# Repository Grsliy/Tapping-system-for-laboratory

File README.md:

# Sistem Logbook Pengunjung Lab berbasis RFID

Sistem pencatatan kunjungan otomatis untuk Laboratorium Power Electronics. Pengunjung yang
sudah terdaftar tinggal tap kartu RFID di pintu masuk, tanpa perlu isi buku tamu fisik.

## Cara kerja

1. Pengunjung mengajukan surat izin kunjungan ke lab, lalu admin mendaftarkan namanya ke
   Google Sheet bersama UID kartu RFID yang akan dipakai.
2. Saat berkunjung, pengunjung tap kartu di reader RFID yang terpasang di pintu masuk.
3. ESP32 membaca UID kartu dan mengirimkannya ke Google Apps Script lewat HTTPS.
4. Apps Script mencocokkan UID ke daftar pengunjung terdaftar, lalu mencatat waktu tap ke
   Google Sheet.
5. Layar pada perangkat menyapa pengunjung dengan namanya, atau memberi tahu bahwa kartunya
   belum terdaftar.

Rincian tiap langkah ada di bagian [Cara Kerja](Dokumen/Sistem-Logbook-Pengunjung-RFID.md#cara-kerja)
di dokumen utama.

## Arsitektur

ESP32 membaca UID kartu lewat modul MFRC522, connect ke jaringan WiFi kampus, lalu
mengirim data tap ke Google Apps Script yang mencocokkan dan mencatatnya ke Google Sheet.
Hasilnya ditampilkan di layar OLED pada perangkat, sehingga alat ini berdiri sendiri di
pintu masuk tanpa komputer yang tersambung.

Detail lengkap arsitektur, varian ESP32 yang dipakai, keputusan teknis, dan skema data ada
di [Dokumen/Sistem-Logbook-Pengunjung-RFID](Dokumen/Sistem-Logbook-Pengunjung-RFID.md).

## Struktur folder

- [Dokumen/](Dokumen/) — rancangan sistem, keputusan arsitektur, dan milestone pengerjaan.
- [Tutorial/](Tutorial/) — panduan langkah kerja per milestone, urut sesuai hari pengerjaan.
- [Referensi/](Referensi/) — materi pendukung (modul praktikum IoT, datasheet modul MFRC522).
- [Gambar/](Gambar/) — foto prototipe, diagram arsitektur, dan skematik rangkaian.
- [PCB/](PCB/) — PCB satu sisi 46×48 mm: berkas KiCad, Gerber, PDF untuk toner transfer, dan
  script pembangunnya.
- [Casing/](Casing/) — casing cetak 3D berbentuk kucing yang memikul kotak elektronik, beserta
  ilustrasi letak PCB di dalamnya. Model kucingnya remix dari
  [Cute Cat Phone Holder](https://www.thingiverse.com/thing:7095121) karya ABoyNamedSue
  (CC BY-SA).
- [logbook-firmware/](logbook-firmware/) — kode firmware ESP32 (PlatformIO, framework Arduino).
- [logbook-appsscript/](logbook-appsscript/) — salinan lokal kode Google Apps Script (backend
  yang jalan di Google, dipakai untuk riwayat/backup di luar Apps Script Editor).

## Status pengerjaan

Status terkini ada di bagian [Status dan Rencana Kerja](Dokumen/Sistem-Logbook-Pengunjung-RFID.md#status-dan-rencana-kerja)
di dokumen utama.

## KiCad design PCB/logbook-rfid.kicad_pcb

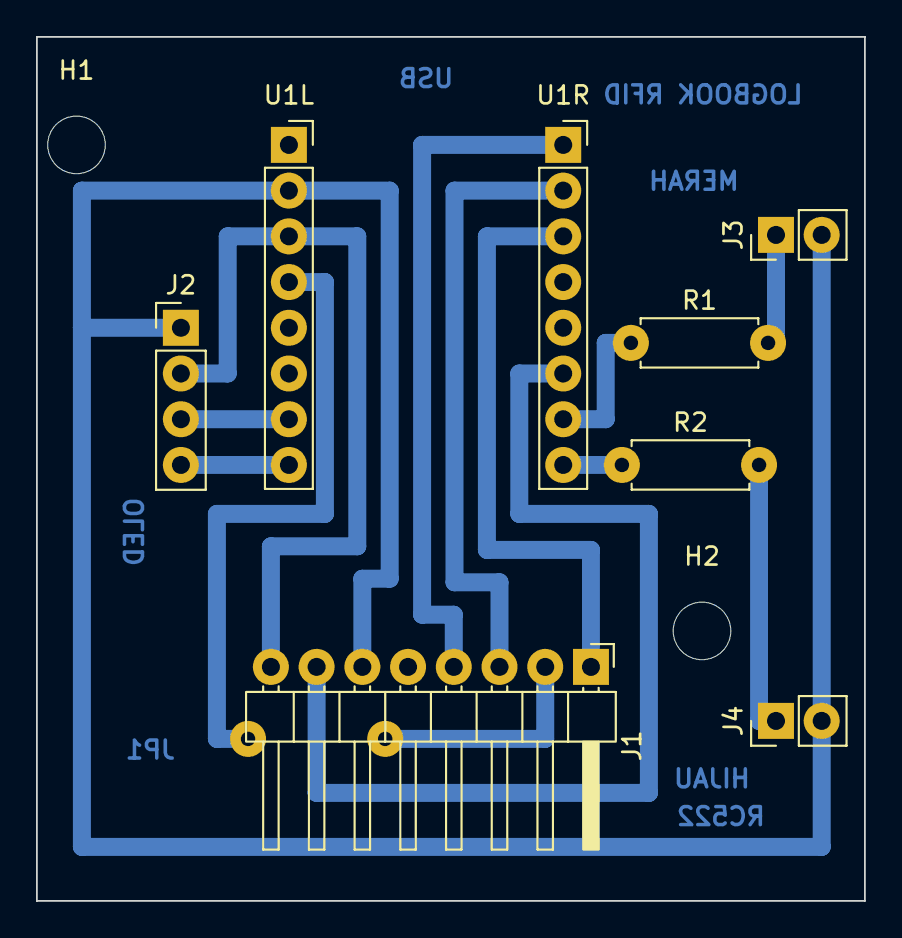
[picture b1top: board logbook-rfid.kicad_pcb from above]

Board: 2 copper layers, 46.0 x 48.0 mm, 11 parts (1 on the bottom side), 13 nets.

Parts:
H1, H2: M3; MountingHole_3.2mm_M3
J1: RC522; PinHeader_1x08_P2.54mm_Horizontal
J2: OLED (solder); PinHeader_1x04_P2.54mm_Vertical
J3: LED merah (solder); PinHeader_1x02_P2.54mm_Vertical
J4: LED hijau (solder); PinHeader_1x02_P2.54mm_Vertical
JP1: kabel berisolasi; R_Axial_DIN0207_L6.3mm_D2.5mm_P7.62mm_Horizontal
R1, R2: 220; R_Axial_DIN0207_L6.3mm_D2.5mm_P7.62mm_Horizontal
U1L: SuperMini kiri; PinSocket_1x08_P2.54mm_Vertical
U1R: SuperMini kanan; PinSocket_1x08_P2.54mm_Vertical

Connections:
3V3: J1.8, J2.2, U1L.3
CS: J1.1, U1R.3
GND: J1.6, J2.1, J3.2, J4.2, U1L.2
LED_G: R2.1, U1R.8
LED_G_A: J4.1, R2.2
LED_R: R1.1, U1R.7
LED_R_A: J3.1, R1.2
MISO: J1.4, U1R.1
MOSI: J1.3, U1R.2
RST: J1.7, U1R.6
SCK: J1.2, JP1.1, U1L.4
SCL: J2.3, U1L.7
SDA: J2.4, U1L.8

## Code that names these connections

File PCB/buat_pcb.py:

"""Bangun PCB single-layer (B.Cu) logbook RFID versi compact, dengan routing manual.

Disesuaikan dengan casing Casing/kucing-kotak-menyatu yang sudah dicetak: PCB di lantai bak, di
bawah modul OLED, komponen menghadap atas, tepi USB menghadap dinding kanan bak. Posisi di bak:
u = 23 - y_pcb, v = 92.2 - x_pcb. Ruang di atas PCB 15.9 mm (di bawah OLED) sampai 20.4 mm. Karena itu:
  lubang M3 di (2.2, 6) dan (36.95, 33), tepat di atas standoff bak (17, 90) dan (-10, 55.25)
  J1 (RC522) header siku, pin rebah ke tepi bawah PCB, dupont menjulur ke dinding kiri bak
  J2 (OLED), J3 (LED merah), dan J4 (LED hijau) tanpa header, kabel disolder langsung ke pad
  (J2 di bawah modul OLED dan dekat dinding belakang bak, tidak ada ruang untuk dupont)
  J3 di sisi kanan bak dan J4 di sisi kiri, searah dengan letak LED merah dan hijau di tutup
  JP1 kabel jumper berisolasi di sisi bawah PCB (sisi atas tertutup dupont J1)
Resistor LED THT tidur di PCB, LED di tutup casing.
"""
import sys
import pcbnew
from pcbnew import VECTOR2I_MM as P, FromMM

out = sys.argv[1]
# Mode 'milling': routing sama, tapi ground fill disederhanakan untuk software CNC yang hang pada
# poligon rumit: tanpa teks tembaga, pad GND tersambung penuh (tanpa thermal relief), dan
# lingkaran dipecah lebih kasar.
MILLING = len(sys.argv) > 2 and sys.argv[2] == 'milling'
LIB = r'C:/Program Files/KiCad/10.0/share/kicad/footprints/'
TRACK_W = 1.0
PAD_D = 2.0
BOARD_W, BOARD_H = 46, 48

b = pcbnew.BOARD()
ds = b.GetDesignSettings()
ds.m_MinClearance = FromMM(0.4)
ds.m_TrackMinWidth = FromMM(0.8)
if MILLING:
    ds.m_MaxError = FromMM(0.05)
ds.SetCopperLayerCount(2)

nets = {}
def net(name):
    if name not in nets:
        n = pcbnew.NETINFO_ITEM(b, name)
        b.Add(n)
        nets[name] = n
    return nets[name]

def place(lib, name, ref, value, x, y, rot=0, pad_d=PAD_D):
    fp = pcbnew.FootprintLoad(LIB + lib + '.pretty', name)
    fp.SetReference(ref)
    fp.SetValue(value)
    b.Add(fp)
    fp.SetPosition(P(x, y))
    fp.SetOrientationDegrees(rot)
    if pad_d:
        for p in fp.Pads():
            p.SetSize(pcbnew.F_Cu, P(pad_d, pad_d))
    return fp

def pos(p):
    q = p.GetPosition()
    return (round(pcbnew.ToMM(q.x), 3), round(pcbnew.ToMM(q.y), 3))

def pin(fp, num, netname):
    p = fp.FindPadByNumber(str(num))
    p.SetNet(net(netname))
    return pos(p)

def track(netname, *pts):
    for a, c in zip(pts, pts[1:]):
        t = pcbnew.PCB_TRACK(b)
        t.SetStart(P(*a))
        t.SetEnd(P(*c))
        t.SetWidth(FromMM(TRACK_W))
        t.SetLayer(pcbnew.B_Cu)
        t.SetNet(net(netname))
        b.Add(t)

def text(s, x, y, size=1.0, rot=0):
    t = pcbnew.PCB_TEXT(b)
    t.SetText(s)
    t.SetPosition(P(x, y))
    t.SetLayer(pcbnew.B_Cu)
    t.SetMirrored(True)
    t.SetTextSize(P(size, size))
    t.SetTextThickness(FromMM(0.2))
    t.SetTextAngleDegrees(rot)
    b.Add(t)

# ===== Komponen =====
# ESP32-C3 SuperMini dilihat dari atas, USB menghadap ke atas (y kecil)
uL = place('Connector_PinSocket_2.54mm', 'PinSocket_1x08_P2.54mm_Vertical', 'U1L', 'SuperMini kiri', 14, 6)
uR = place('Connector_PinSocket_2.54mm', 'PinSocket_1x08_P2.54mm_Vertical', 'U1R', 'SuperMini kanan', 29.24, 6)
# J1 pin 1 = SDA RC522 di ujung kanan, pin 8 = 3.3V di ujung kiri; header siku, pin rebah ke +y
# (tepi bawah papan) karena tepat di atasnya ada modul OLED
j1 = place('Connector_PinHeader_2.54mm', 'PinHeader_1x08_P2.54mm_Horizontal', 'J1', 'RC522', 30.78, 35, 270)
# J2 ke OLED, tanpa header (kabel disolder langsung). Urutan mengikuti modul OLED yang dipakai:
# GND, VDD, SCK, SDA (modul lain ada yang VCC, GND, ...; cek label modul sebelum menyambung)
j2 = place('Connector_PinHeader_2.54mm', 'PinHeader_1x04_P2.54mm_Vertical', 'J2', 'OLED (solder)', 8, 16.16)
# Pad solder LED (anoda, GND), dipisah supaya masing-masing dekat LED-nya di tutup casing:
# J3 merah di dekat tepi atas PCB (sisi kanan bak), J4 hijau di dekat tepi bawah (sisi kiri bak).
j3 = place('Connector_PinHeader_2.54mm', 'PinHeader_1x02_P2.54mm_Vertical', 'J3', 'LED merah (solder)', 41.06, 11, 90)
j4 = place('Connector_PinHeader_2.54mm', 'PinHeader_1x02_P2.54mm_Vertical', 'J4', 'LED hijau (solder)', 41.06, 38, 90)
r1 = place('Resistor_THT', 'R_Axial_DIN0207_L6.3mm_D2.5mm_P7.62mm_Horizontal', 'R1', '220', 33, 17)
r2 = place('Resistor_THT', 'R_Axial_DIN0207_L6.3mm_D2.5mm_P7.62mm_Horizontal', 'R2', '220', 32.5, 23.78)
jp1 = place('Resistor_THT', 'R_Axial_DIN0207_L6.3mm_D2.5mm_P7.62mm_Horizontal', 'JP1', 'kabel berisolasi', 11.73, 39)
# Sisi atas di titik ini tertutup dupont J1, jadi JP1 dipasang di sisi bawah (ruang standoff 5 mm)
# sebagai kabel berisolasi. Dibalik atas-bawah supaya posisi pad tetap.
jp1.Flip(jp1.GetPosition(), pcbnew.FLIP_DIRECTION_TOP_BOTTOM)
# Dua pad bernomor sama = disambung kabel, supaya DRC tidak menganggapnya putus
jp1.SetDuplicatePadNumbersAreJumpers(True)
jp1.FindPadByNumber('2').SetNumber('1')
HOLES = [(2.2, 6), (36.95, 33)]   # di atas standoff bak yang sudah dicetak
for i, (x, y) in enumerate(HOLES):
    place('MountingHole', 'MountingHole_3.2mm_M3', f'H{i+1}', 'M3', x, y, pad_d=None)

# ===== Pad ke net =====
L = {2: pin(uL, 2, 'GND'), 3: pin(uL, 3, '3V3'), 4: pin(uL, 4, 'SCK'),
     7: pin(uL, 7, 'SCL'), 8: pin(uL, 8, 'SDA')}
R = {1: pin(uR, 1, 'MISO'), 2: pin(uR, 2, 'MOSI'), 3: pin(uR, 3, 'CS'),
     6: pin(uR, 6, 'RST'), 7: pin(uR, 7, 'LED_R'), 8: pin(uR, 8, 'LED_G')}
J1 = {1: pin(j1, 1, 'CS'), 2: pin(j1, 2, 'SCK'), 3: pin(j1, 3, 'MOSI'), 4: pin(j1, 4, 'MISO'),
      6: pin(j1, 6, 'GND'), 7: pin(j1, 7, 'RST'), 8: pin(j1, 8, '3V3')}
J2 = {1: pin(j2, 1, 'GND'), 2: pin(j2, 2, '3V3'), 3: pin(j2, 3, 'SCL'), 4: pin(j2, 4, 'SDA')}
J3 = {1: pin(j3, 1, 'LED_R_A'), 2: pin(j3, 2, 'GND')}
J4 = {1: pin(j4, 1, 'LED_G_A'), 2: pin(j4, 2, 'GND')}
R1 = (pin(r1, 1, 'LED_R'), pin(r1, 2, 'LED_R_A'))
R2 = (pin(r2, 1, 'LED_G'), pin(r2, 2, 'LED_G_A'))
for p in jp1.Pads():
    p.SetNet(net('SCK'))
JP = tuple(sorted(pos(p) for p in jp1.Pads()))
print('J1', J1); print('J3', J3); print('R1', R1, 'R2', R2); print('JP', JP)

# ===== Routing B.Cu =====
# I2C langsung ke kiri
track('SCL', L[7], J2[3])
track('SDA', L[8], J2[4])
# 3V3: ke OLED (J2 pin 2) masuk dari kanan, ke RC522 lewat bawah modul
track('3V3', L[3], (10.6, 11.08), (10.6, 18.70), J2[2])
track('3V3', L[3], (17.8, 11.08), (17.8, 28.3), (13, 28.3), J1[8])
# GND: ke OLED (J2 pin 1) dan LED lewat tepi papan, ke RC522 lewat bawah modul
track('GND', L[2], (2.5, 8.54), (2.5, 16.16), J2[1])
track('GND', (2.5, 16.16), (2.5, 45), (43.6, 45), J4[2])
track('GND', J4[2], J3[2])
track('GND', L[2], (19.6, 8.54), (19.6, 30.1), (18.08, 30.1), J1[6])
# SPI
track('MISO', R[1], (21.4, 6), (21.4, 32.1), (23.16, 32.1), J1[4])
track('MOSI', R[2], (23.2, 8.54), (23.2, 30.3), (25.70, 30.3), J1[3])
track('CS', R[3], (25.0, 11.08), (25.0, 28.5), (30.78, 28.5), J1[1])
track('SCK', L[4], (16.0, 13.62), (16.0, 26.5), (10, 26.5), (10, 39), JP[0])
track('SCK', JP[1], (28.24, 39), J1[2])
track('RST', R[6], (26.8, 18.70), (26.8, 26.5), (34, 26.5), (34, 42), (15.54, 42), J1[7])
# LED status: resistor di PCB, LED di casing lewat J3
track('LED_R', R[7], (31.6, 21.24), (31.6, 17), R1[0])
track('LED_R_A', R1[1], (41.06, 17), J3[1])
track('LED_G', R[8], R2[0])
track('LED_G_A', R2[1], (40.12, 38), J4[1])

# ===== Outline =====
rect = pcbnew.PCB_SHAPE(b)
rect.SetShape(pcbnew.SHAPE_T_RECT)
rect.SetStart(P(0, 0))
rect.SetEnd(P(BOARD_W, BOARD_H))
rect.SetLayer(pcbnew.Edge_Cuts)
rect.SetWidth(FromMM(0.1))
b.Add(rect)

# ===== Label tembaga (dibaca dari sisi bawah) =====
if not MILLING:
    text('USB', 21.62, 2.3)
    text('LOGBOOK RFID', 37, 3.2)
    text('MERAH', 36.5, 8)
    text('HIJAU', 37.5, 41.2)
    text('RC522', 38, 43.3)
    text('JP1', 6.3, 39.6)
    text('OLED', 5.4, 27.5, 1.0, 90)

# ===== Ground fill B.Cu =====
# Jalur GND tetap ada sebagai tulang punggung; fill menyambung semuanya dan mengurangi
# tembaga yang harus dietsa.
FILL_CLEARANCE = 0.6
zone = pcbnew.ZONE(b)
zone.SetLayer(pcbnew.B_Cu)
zone.SetNet(net('GND'))
outline = zone.Outline()
outline.NewOutline()
for x, y in [(0, 0), (BOARD_W, 0), (BOARD_W, BOARD_H), (0, BOARD_H)]:
    outline.Append(FromMM(x), FromMM(y))
zone.SetLocalClearance(FromMM(FILL_CLEARANCE))
zone.SetMinThickness(FromMM(0.5))
zone.SetPadConnection(pcbnew.ZONE_CONNECTION_FULL if MILLING else pcbnew.ZONE_CONNECTION_THERMAL)
zone.SetThermalReliefGap(FromMM(0.6))
zone.SetThermalReliefSpokeWidth(FromMM(0.8))
zone.SetIslandRemovalMode(pcbnew.ISLAND_REMOVAL_MODE_ALWAYS)
b.Add(zone)
# ZONE_FILLER dari Python crash di KiCad 10.0-rc1; isi zone dengan:
#   kicad-cli pcb drc --refill-zones --save-board logbook-rfid.kicad_pcb

b.Save(out)
print('saved', out)
